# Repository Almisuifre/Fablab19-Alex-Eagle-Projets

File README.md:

# Fablab19-Alex-Eagle-Projets
Projets Eagle fait au Fablab 19

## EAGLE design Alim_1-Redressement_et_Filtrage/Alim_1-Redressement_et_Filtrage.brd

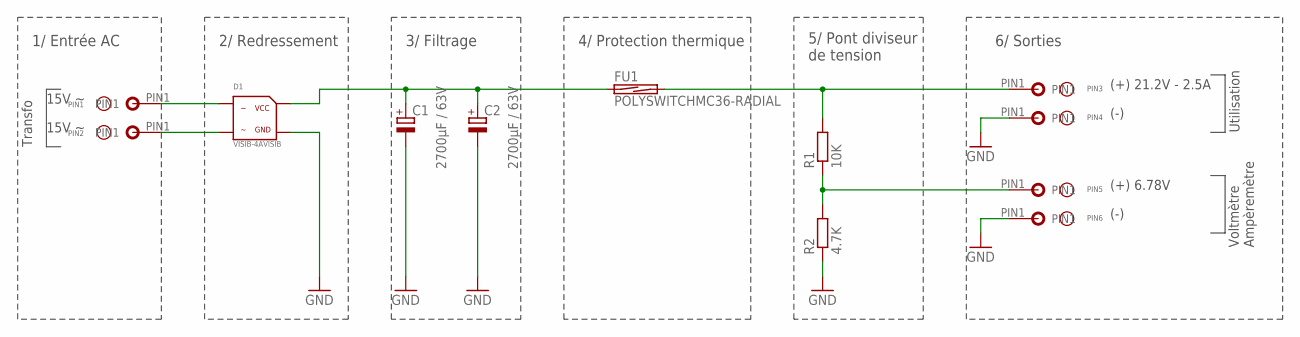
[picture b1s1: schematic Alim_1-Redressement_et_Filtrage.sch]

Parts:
C1, C2: 2700µF / 63V; EB25D
D1: VISIB-4AVISIB; VISIB-4A
FU1: POLYSWITCHMC36-RADIAL; MC36253-RADIAL
PIN1, PIN2, PIN3, PIN4, PIN5, PIN6: CON-FILTRAVERSANT-1FILTRAVERSANT-1; CON-FILTRAVERSANT-1
R1: 10K; R0805
R2: 4.7K; R0805

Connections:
GND: C1.-, C2.-, D1.GND, PIN4.PIN1, PIN6.PIN1, R2.1
unnamed: D1.ALT1, PIN1.PIN1
unnamed: D1.ALT2, PIN2.PIN1
unnamed: C1.+, C2.+, D1.VCC, FU1.1
unnamed: PIN5.PIN1, R1.1, R2.2
unnamed: FU1.2, PIN3.PIN1, R1.2

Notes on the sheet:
15V ~
Transfo
1/ Entrée AC
2/ Redressement
3/ Filtrage
4/ Protection thermique
5/ Pont diviseur de tension
6/ Sorties
(+) 21.2V - 2.5A
(-)
(+) 6.78V
Utilisation
Voltmètre Ampèremètre

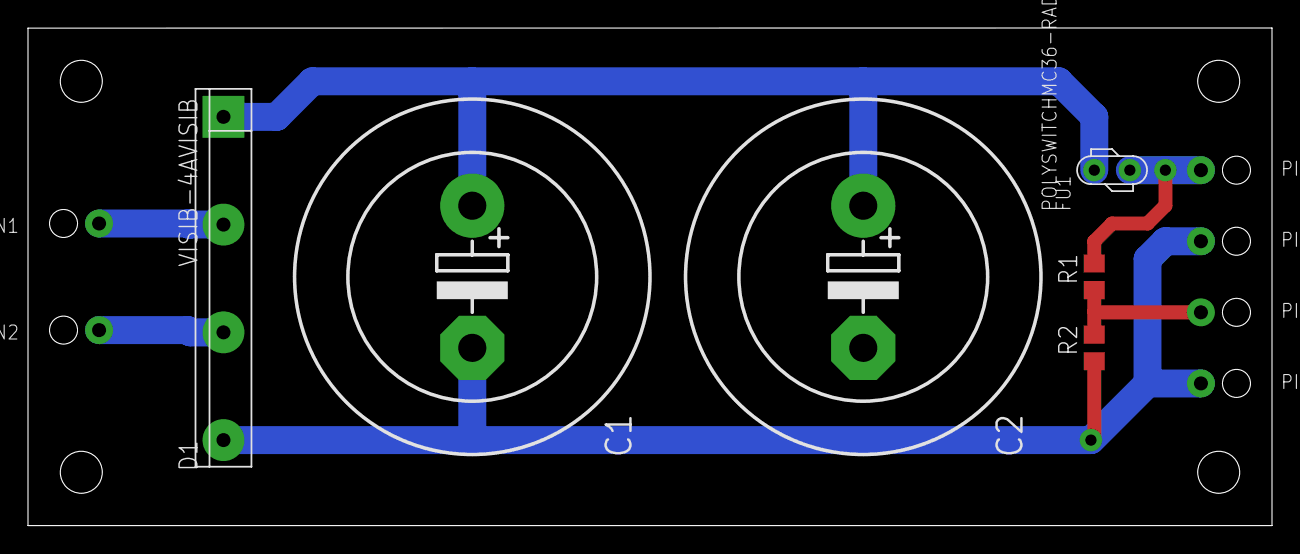
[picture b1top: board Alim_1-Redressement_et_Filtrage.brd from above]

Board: 2 copper layers, 88.9 x 35.6 mm, 12 parts (0 on the bottom side), 6 nets.

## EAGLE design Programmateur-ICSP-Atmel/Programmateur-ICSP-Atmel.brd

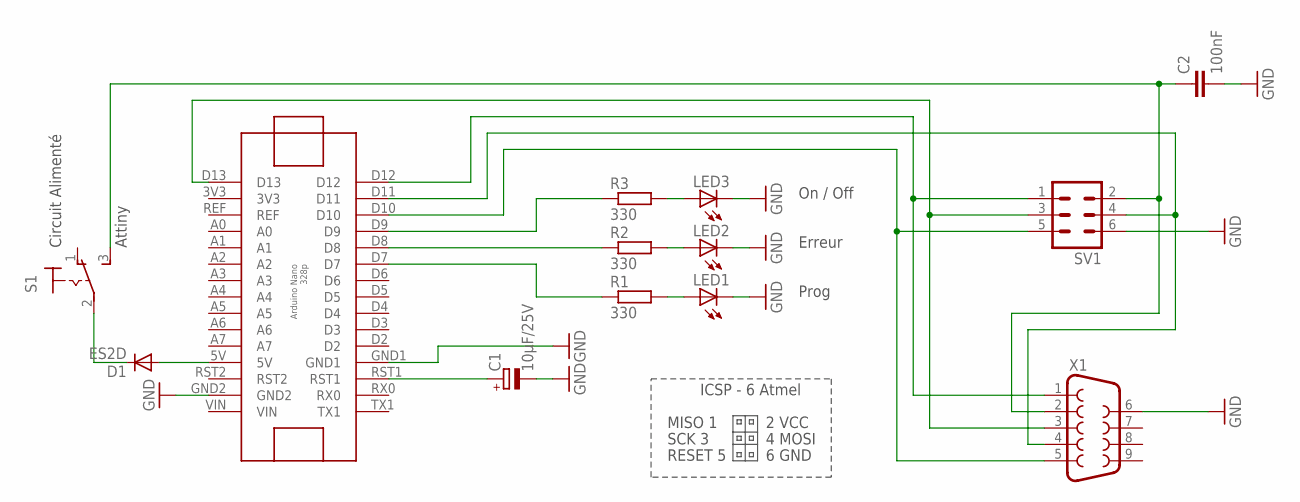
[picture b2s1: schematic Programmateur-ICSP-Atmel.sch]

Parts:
ARDUINO-NANO1: ARDUINO-NANO
C1: 10µF/25V; E2,5-5
C2: 100nF; C0805
D1: ES2D; SMB
LED1, LED2, LED3: LED5MM
R1, R2, R3: 330; R0805
S1: 320-916
SV1: ML6L
X1: F09HP

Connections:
GND: ARDUINO-NANO1.GND1, ARDUINO-NANO1.GND2, C1.-, C2.2, LED1.K (C), LED2.K (C), LED3.K (C), SV1.6, X1.6
MISO: ARDUINO-NANO1.D12, SV1.1, X1.1
MOSI: ARDUINO-NANO1.D11, SV1.4, X1.4
unnamed: LED1.A, R1.2
unnamed: ARDUINO-NANO1.D7, R1.1
unnamed: ARDUINO-NANO1.D8, R2.1
unnamed: LED2.A, R2.2
unnamed: ARDUINO-NANO1.D9, R3.1
unnamed: LED3.A, R3.2
unnamed: ARDUINO-NANO1.5V, D1.A
unnamed: ARDUINO-NANO1.RST1, C1.+
unnamed: D1.C, S1.2
RESET: ARDUINO-NANO1.D10, SV1.5, X1.5
SCK: ARDUINO-NANO1.D13, SV1.3, X1.3
VCC: C2.1, S1.3 (S), SV1.2, X1.2

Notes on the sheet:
Prog
Erreur
On / Off
MISO 1
SCK 3
RESET 5
2 VCC
4 MOSI
6 GND
ICSP - 6 Atmel
Attiny
Circuit Alimenté

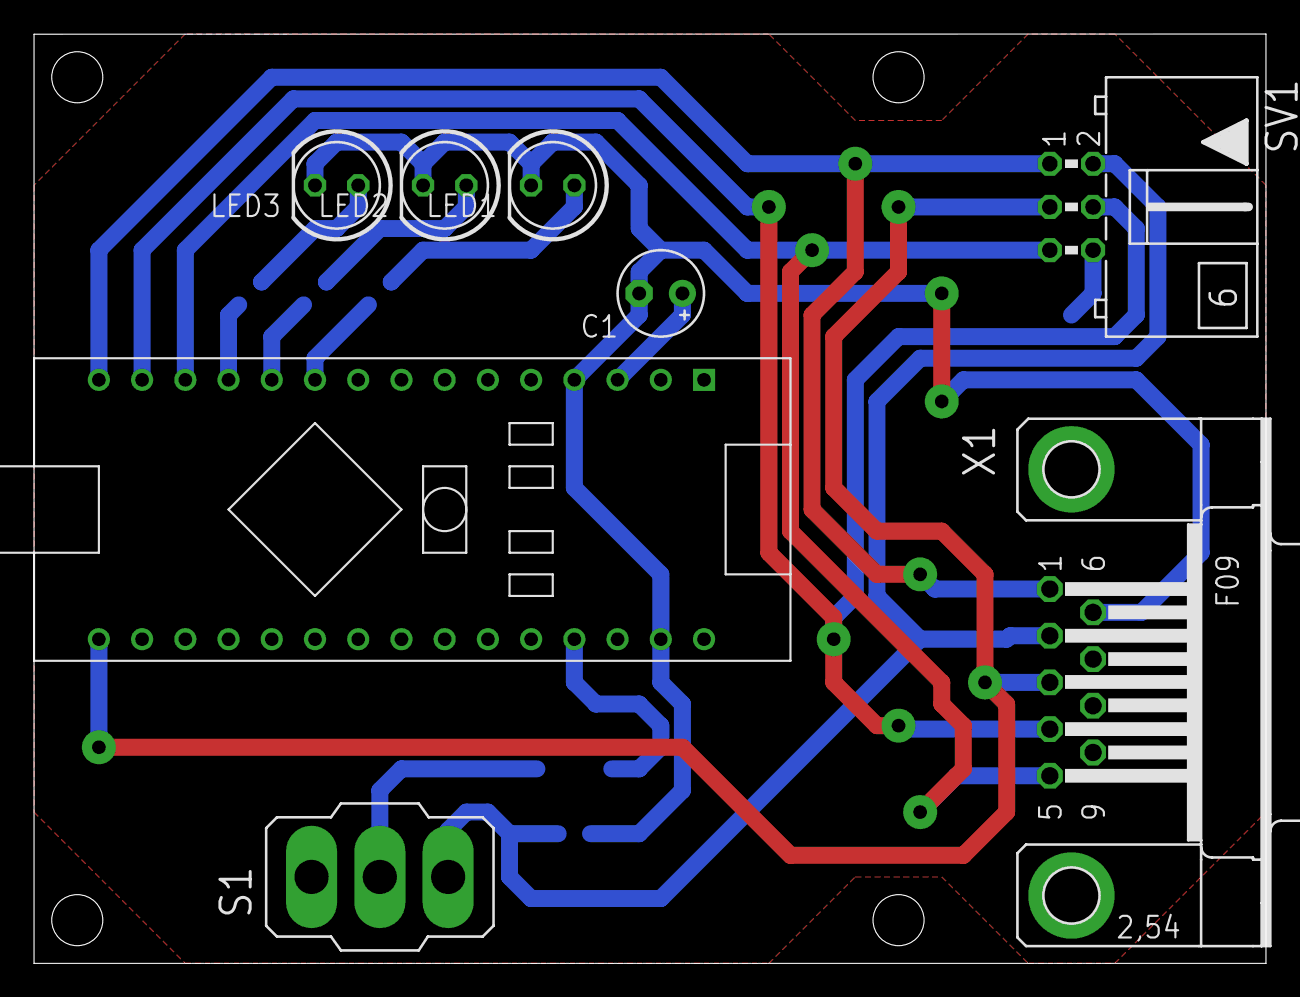
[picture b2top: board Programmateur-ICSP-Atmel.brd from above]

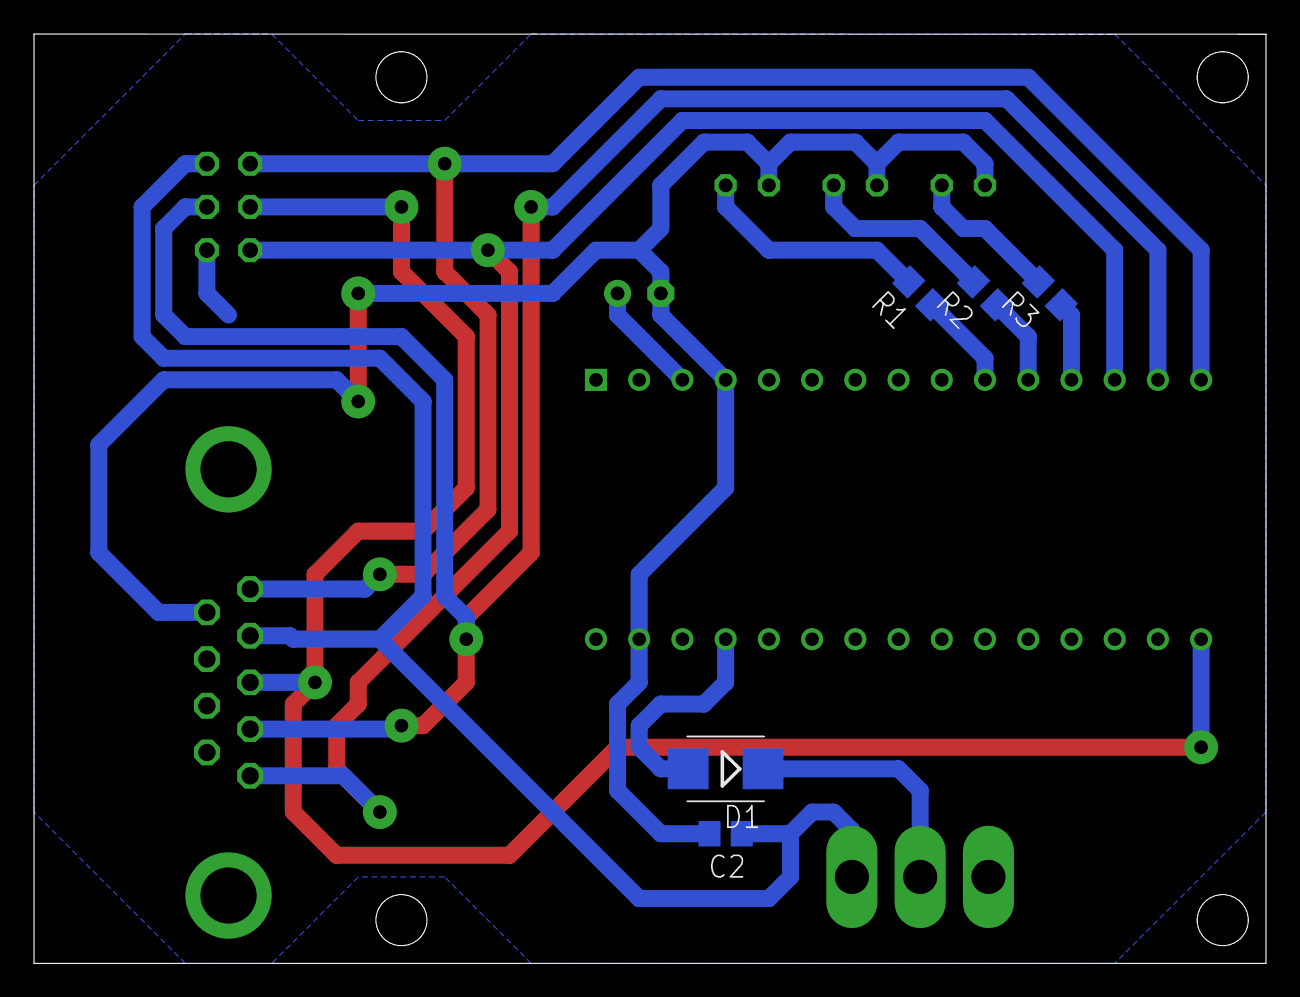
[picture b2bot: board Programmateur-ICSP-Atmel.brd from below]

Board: 2 copper layers, 72.4 x 54.6 mm, 13 parts (5 on the bottom side), 15 nets.

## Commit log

2018-02-10 Add project from eagle
    Add project from eagle
